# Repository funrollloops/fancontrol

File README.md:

## Overview
v1 used an arduino nano with a custom PCB on top, but the result was thick and ungainly. v2 uses a pcb with an stm32 integrated on board,
but still expects to use an OLED on a 4-pin carrier board. This does fit inside a Meshlicious alongside a 280mm rad, but it could be more elegant.

v2 includes a USB port, but it's not really used by the firmware. Removing it in v3 might allow for a sleeker design that is easier to put in a case.

### Clearance inside Meshlicious
Total available clearance is 10mm:

* 1.6mm PCB
* 6.5mm for right angle fan header on back
* 6.3mm for the oled display module
    * 1.6mm for the PCB
    * 1.6mm for the display
    * 3.1mm for the JST connector (1.1mm for components w/o connector)

So will need to use a bare oled display and use an FPC connector to save space.
All components will be on the top side of the PCB, which will face towards the
radiator/fan where the fan connectors come out.

## Schematic

See the pcb/ directory. Designed for PCBA via JLCPCB, using only one extended part (the USB-C connector). Costs $20 shipped for 5x.

## Firmware

Install [STM32CubeProgrammer](https://www.st.com/en/development-tools/stm32cubeprog.html) somewhere, and then build and flash with
```
cmake -S. -Bbuild -DCMAKE_BUILD_TYPE=Release -GNinja -DSTM32_CUBE_PROGRAMMER=/path/to/STM32_Programmer_CLI
ninja -Cbuild flash
```

## Design

## Calibration

WIP, will log CPU/GPU/thermistor readings to create a calibration table.  According to the datasheet,
given some inputs the output formula should be:

```py
# Circuit: VCC - R2 - thermistor - GND
#                   ⌞ ADC

VCC = 5
AREF = 3.3
R2 = 33_000

def C(adc):
    """adc is the voltage across the thermistor when it is in series with R2, where 0=0V and 1024=AREF."""
    return 227 - 34.3 * ln(adc)
```

But a lookup table is probably simpler since only ~1C accuracy is needed and there's no FPU anyway.

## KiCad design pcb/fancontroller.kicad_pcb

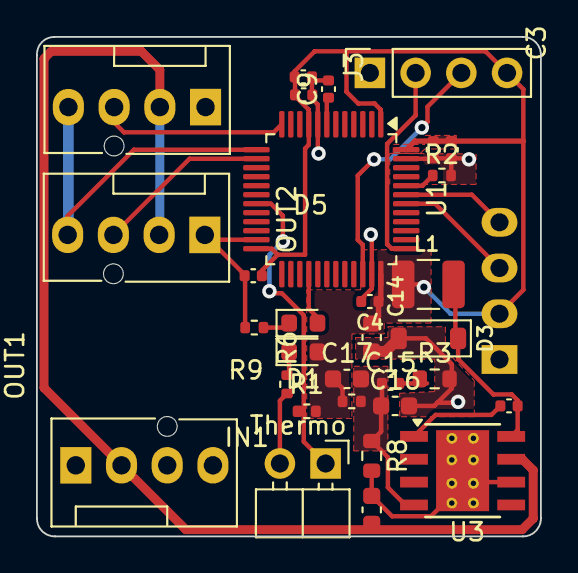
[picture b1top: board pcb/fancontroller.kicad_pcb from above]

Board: 2 copper layers, 28.0 x 27.8 mm, 32 parts (1 on the bottom side), 20 nets.

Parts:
C1: 4.7uF; C_0402_1005Metric
C2, C3, C4, C15: 100nF; C_0402_1005Metric
C5: 1uF; C_0402_1005Metric
C6, C13: 10nF; C_0402_1005Metric
C9: 100n; C_0402_1005Metric
C12: 10uF; C_0603_1608Metric
C14: 22uF; C_0603_1608Metric
C16: 150pF; C_0603_1608Metric
C17: 1.5nF; C_0603_1608Metric
D1, D5: white; LED_0603_1608Metric
D3: B5819W; D_SOD-123
IN1: FAN_HEADER; FanPinHeader_1x04_P2.54mm_Vertical
J1: Thermo; PinHeader_1x02_P2.54mm_Horizontal
J3: SWD; PinSocket_1x04_P2.54mm_Vertical
L1: 10uH; L_1210_3225Metric
OUT1, OUT2: FAN_HEADER; FanPinHeader_1x04_P2.54mm_Vertical
R1: 33kΩ; R_0402_1005Metric
R2: 5.1kΩ; R_0402_1005Metric
R3: 549Ω; R_0603_1608Metric
R6, R9: 1.5kΩ; R_0402_1005Metric
R7: 10kΩ; R_0402_1005Metric
R8: 5.9kΩ; R_0603_1608Metric
SSD1306: SSD1306; 128x64OLED
U1: STM32F103C8Tx; LQFP-48_7x7mm_P0.5mm
U3: TPS5430DDA; TI_SO-PowerPAD-8_ThermalVias

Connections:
+3.3V: C1.1, C2.1, C3.1, C4.1, C5.1, C6.1, C14.1, C17.1, D1.2 (A), J3.4, L1.2, R1.1, R7.1, SSD1306.2 (VCC), U1.1 (VBAT), U1.9 (VDDA), U1.24 (VDD), U1.36 (VDD), U1.48 (VDD)
+12V: C12.1, IN1.2 (+), OUT1.2 (+), OUT2.2 (+), U3.7 (VIN)
/APP_LED: D5.1 (K), R9.1
/BOOT0: R2.1, U1.44 (BOOT0)
/NRST: C9.1, U1.7 (NRST)
/PFSENSE: C15.1, C16.1, C17.2, R7.2, R8.1, U3.4 (VSENSE)
/PLED_K: D1.1 (K), R6.1
/PWM: OUT1.4 (PWM), OUT2.4 (PWM), U1.13 (PA3)
/SCL: SSD1306.3 (SCL), U1.42 (PB6)
/SDA: SSD1306.4 (SDA), U1.43 (PB7)
/SWCLK: J3.2, U1.37 (PA14)
/SWDIO: J3.3, U1.34 (PA13)
/TACH1: IN1.3 (Tacho), OUT1.3 (Tacho), U1.14 (PA4)
/TACH2: OUT2.3 (Tacho), U1.12 (PA2)
/TEMP: J1.1, R1.2, U1.19 (PB1)
GND: C1.2, C2.2, C3.2, C4.2, C5.2, C6.2, C9.2, C12.2, C14.2, C16.2, D3.2 (A), IN1.1 (-), J1.2, J3.1, OUT1.1 (-), OUT2.1 (-), R2.2, R3.2, R6.2, R8.2, R9.2, SSD1306.1 (GND), U1.8 (VSSA), U1.23 (VSS), U1.35 (VSS), U1.47 (VSS), U3.6 (GND), U3.9 (GNDPAD)
unnamed: C15.2, R3.1
unnamed: C13.2, D3.1 (K), L1.1, U3.8 (PH)
unnamed: D5.2 (A), U1.28 (PB15)
unnamed: C13.1, U3.1 (BOOT)

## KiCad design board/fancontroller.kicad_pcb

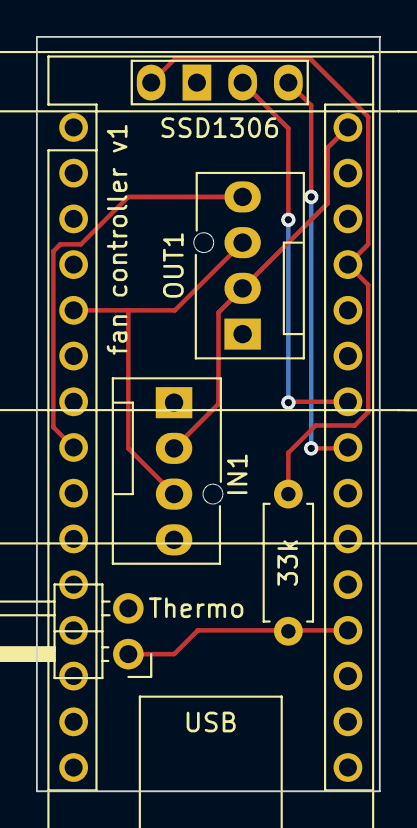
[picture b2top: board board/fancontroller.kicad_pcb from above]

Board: 2 copper layers, 19.0 x 41.9 mm, 6 parts (0 on the bottom side), 8 nets.

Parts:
A1: Arduino_Nano_v3.x; Arduino_Nano
IN1: FAN_HEADER; FanPinHeader_1x04_P2.54mm_Vertical
J1: Thermo; PinHeader_1x02_P2.54mm_Horizontal
OUT1: FAN_HEADER; FanPinHeader_1x04_P2.54mm_Vertical
R1: 33k; R_Axial_DIN0207_L6.3mm_D2.5mm_P7.62mm_Horizontal
SSD1306: SSD1306; 128x64OLED

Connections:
+12V: A1.30 (VIN), IN1.2 (+), OUT1.2 (+)
GND: A1.4 (GND), A1.29 (GND), IN1.1 (-), J1.2, OUT1.1 (-), SSD1306.1 (GND)
unnamed: A1.27 (+5V), R1.1, SSD1306.2 (VCC)
unnamed: A1.19 (A0), J1.1, R1.2
unnamed: A1.23 (A4), SSD1306.4 (SDA)
unnamed: A1.24 (A5), SSD1306.3 (SCL)
unnamed: A1.5 (D2), IN1.3 (Tacho), OUT1.3 (Tacho)
unnamed: A1.8 (D5), OUT1.4 (PWM)

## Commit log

2023-12-29 Fan control test scripts
2023-12-29 Add README.md
2023-12-29 Move firmware into a subdirectory
2024-01-22 v1 PCB revision + working firmware
2024-01-24 Delete calibration directory
    Not needed; manually calibrated using my multimeter.
2024-01-25 attiny85 code that compiles and uploads, but doesn't work
2024-05-15 makefile: fix typo
2024-05-15 makefile: add flash target
2024-05-15 better formatting for rpm>10k
2024-05-15 Add comment translating 20C to 68F
2024-05-15 Format and add priming logic
2024-05-17 Rename board=>pcb
2024-05-17 Change linear region to 40-50C
2024-06-02 Update to Kicad 8, clean up schematic, add second fan header to schematic
2024-06-02 wip: switch to stm32f103
2024-06-09 v2: add stm32cubemx config, early draft of pcb layout, update version
2024-06-09 v2: more stm32cubemx, start generating code
2024-06-10 firmware/{stm32cubemx => }
2024-06-10 Finish routing assuming OLED module
2024-06-10 Blink an LED
2024-06-12 Get PWM, ADC, and gpio interrupts working
2024-06-12 Enable LTO
2024-06-12 Hook table generation into the build
2024-06-14 v2 firmware: add in display, temp, pwm calculation
2024-06-14 Format data more nicely on the display
2024-06-20 add app led, commit attempts to use 0.91" display
2024-06-20 Add LED
2024-06-23 Add fp-info-cache to .gitignore
2024-07-06 Begin rev3: drop USB connector, plan for OLED mounting
